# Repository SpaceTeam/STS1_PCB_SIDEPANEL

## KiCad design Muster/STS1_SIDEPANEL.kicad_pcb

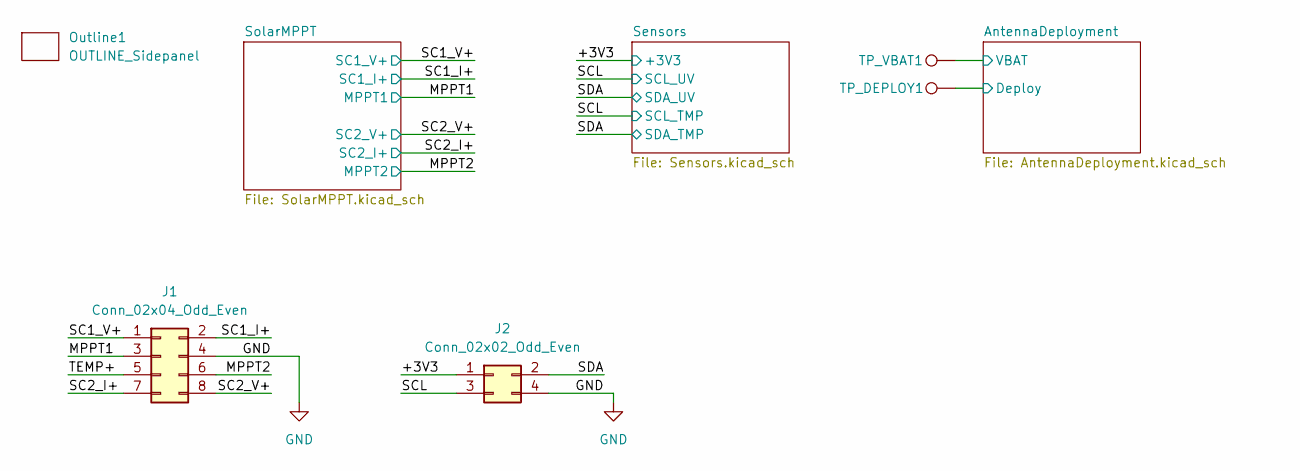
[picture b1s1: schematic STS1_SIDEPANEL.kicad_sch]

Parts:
J1: Conn_02x04_Odd_Even; M808280842
J2: Conn_02x02_Odd_Even; M80-8280442
Outline1: OUTLINE_Sidepanel; OUTLINE_SidepanelZ+
TP_DEPLOY1: TestPoint; TestPoint_Loop_D1.80mm_Drill1.0mm_Beaded
TP_VBAT1: TestPoint; TestPoint_Loop_D1.80mm_Drill1.0mm_Beaded

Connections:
/AntennaDeployment/Deploy: TP_DEPLOY1.1; also elsewhere on the board
/AntennaDeployment/VBAT: TP_VBAT1.1; also elsewhere on the board
/MPPT1: J1.3; also elsewhere on the board
/MPPT2: J1.6; also elsewhere on the board
/SC1_I+: J1.2; also elsewhere on the board
/SC1_V+: J1.1; also elsewhere on the board
/SC2_I+: J1.7; also elsewhere on the board
/SC2_V+: J1.8; also elsewhere on the board
/SCL: J2.3; also elsewhere on the board
/SDA: J2.2; also elsewhere on the board
/TEMP+: J1.5
GND: J1.4, J2.4; also elsewhere on the board

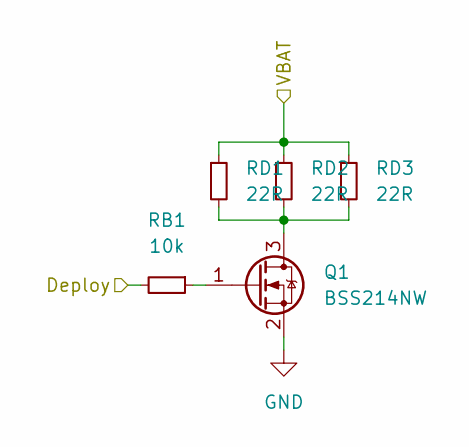
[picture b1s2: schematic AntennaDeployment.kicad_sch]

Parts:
Q1: BSS214NW; SOT-323_SC-70
RB1: 10k; R_0603_1608Metric
RD1, RD2, RD3: 22R; R_MiniMELF_MMA-0204

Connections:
/AntennaDeployment/Deploy: RB1.2; also elsewhere on the board
/AntennaDeployment/VBAT: RD1.1, RD2.1, RD3.1; also elsewhere on the board
GND: Q1.2 (S); also elsewhere on the board
unnamed: Q1.1 (G), RB1.1
unnamed: Q1.3 (D), RD1.2, RD2.2, RD3.2

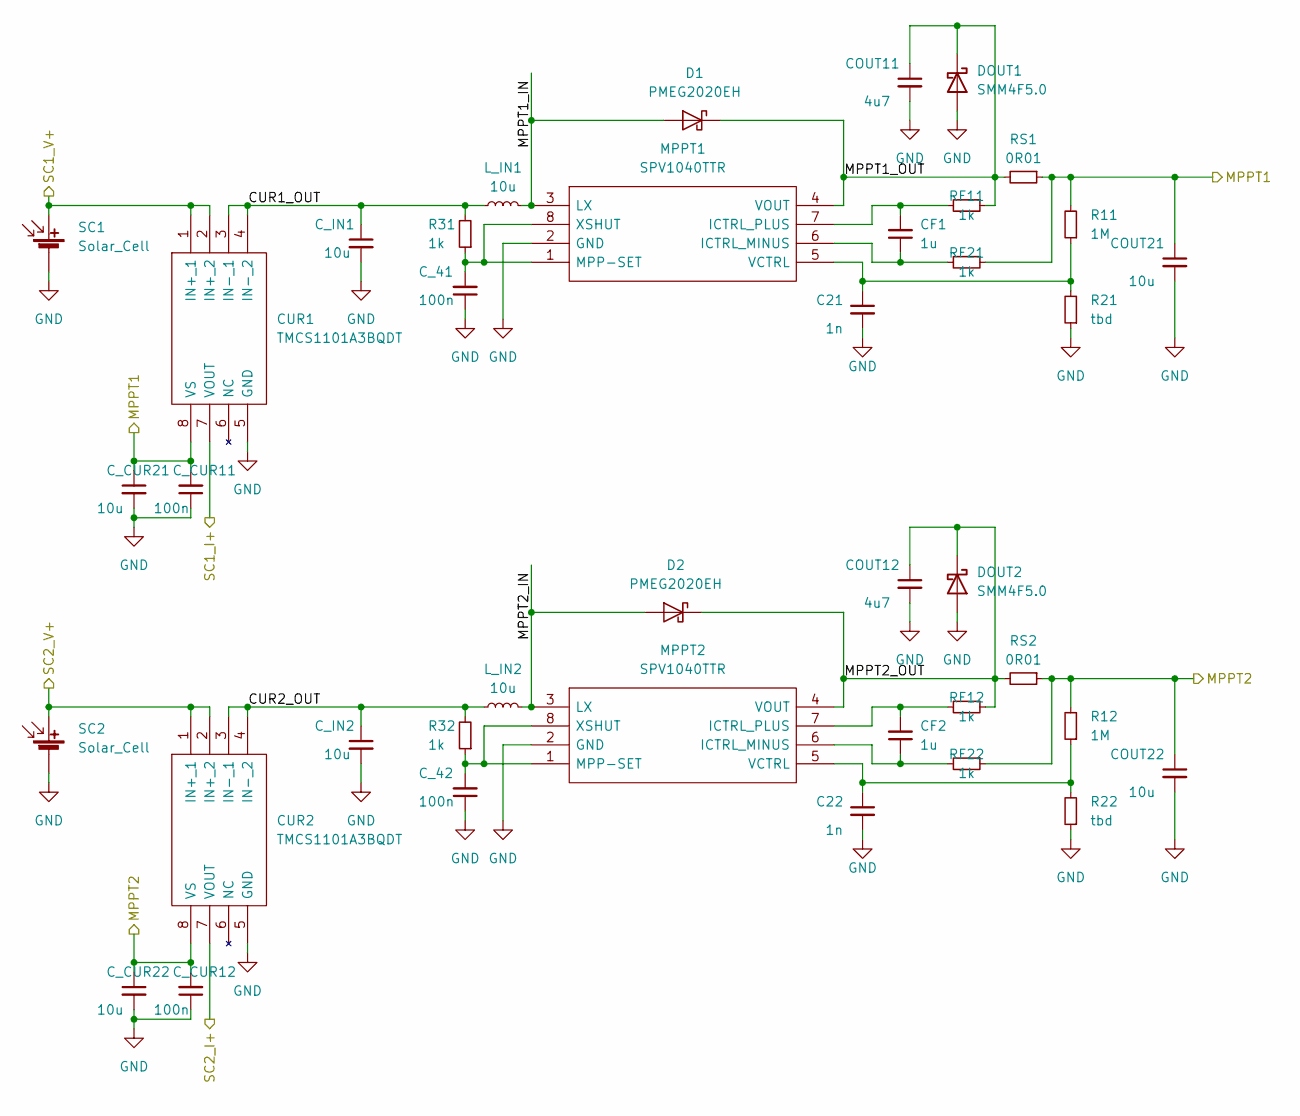
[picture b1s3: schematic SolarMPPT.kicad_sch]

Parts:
C21, C22: 1n; C_0603_1608Metric
CF1, CF2: 1u; C_0603_1608Metric
COUT11, COUT12: 4u7; C_0603_1608Metric
COUT21, COUT22: 10u; C_0603_1608Metric
CUR1, CUR2: TMCS1101A3BQDT; SOIC127P600X175-8N; Mouser Part Number 595-TMCS1101A3BQDT
C_41, C_42: 100n; C_0603_1608Metric
C_CUR11, C_CUR12: 100n; C_0603_1608Metric
C_CUR21, C_CUR22: 10u; C_0603_1608Metric
C_IN1, C_IN2: 10u; C_0603_1608Metric
D1, D2: PMEG2020EH; D_SOD-123F
DOUT1, DOUT2: SMM4F5.0; STMITE
L_IN1, L_IN2: 10u; INDPM5650X530N
MPPT1, MPPT2: SPV1040TTR; SOP65P640X120-8N; Mouser Part Number 511-SPV1040TTR
R11, R12: 1M; R_0603_1608Metric
R21, R22: tbd; R_0603_1608Metric
R31, R32: 1k; R_0603_1608Metric
RF11, RF12, RF21, RF22: 1k; R_0603_1608Metric
RS1, RS2: 0R01; R_0603_1608Metric
SC1, SC2: Solar_Cell; 3G30A_40x80

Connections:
/MPPT1: COUT21.1, CUR1.8 (VS), C_CUR11.2, C_CUR21.1, R11.2, RF21.1, RS1.1; also elsewhere on the board
/MPPT2: COUT22.1, CUR2.8 (VS), C_CUR12.2, C_CUR22.1, R12.2, RF22.1, RS2.1; also elsewhere on the board
/SC1_I+: CUR1.7 (VOUT); also elsewhere on the board
/SC1_V+: CUR1.1 (IN+_1), CUR1.2 (IN+_2), SC1.1 (+); also elsewhere on the board
/SC2_I+: CUR2.7 (VOUT); also elsewhere on the board
/SC2_V+: CUR2.1 (IN+_1), CUR2.2 (IN+_2), SC2.1 (+); also elsewhere on the board
/SolarMPPT/CUR1_OUT: CUR1.3 (IN-_1), CUR1.4 (IN-_2), C_IN1.1, L_IN1.1, R31.2
/SolarMPPT/CUR2_OUT: CUR2.3 (IN-_1), CUR2.4 (IN-_2), C_IN2.1, L_IN2.1, R32.2
/SolarMPPT/MPPT1_IN: D1.2 (A), L_IN1.2, MPPT1.3 (LX)
/SolarMPPT/MPPT1_OUT: COUT11.1, D1.1 (K), DOUT1.1 (K), MPPT1.4 (VOUT), RF11.1, RS1.2
/SolarMPPT/MPPT2_IN: D2.2 (A), L_IN2.2, MPPT2.3 (LX)
/SolarMPPT/MPPT2_OUT: COUT12.1, D2.1 (K), DOUT2.1 (K), MPPT2.4 (VOUT), RF12.1, RS2.2
GND: C21.2, C22.2, COUT11.2, COUT12.2, COUT21.2, COUT22.2, CUR1.5 (GND), CUR2.5 (GND), C_41.1, C_42.1, C_CUR11.1, C_CUR12.1, C_CUR21.2, C_CUR22.2, C_IN1.2, C_IN2.2, DOUT1.2 (A), DOUT2.2 (A), MPPT1.2 (GND), MPPT2.2 (GND), R21.1, R22.1, SC1.2 (-), SC2.2 (-); also elsewhere on the board
unnamed: C21.1, MPPT1.5 (VCTRL), R11.1, R21.2
unnamed: C22.1, MPPT2.5 (VCTRL), R12.1, R22.2
unnamed: CF1.1, MPPT1.6 (ICTRL_MINUS), RF21.2
unnamed: CF1.2, MPPT1.7 (ICTRL_PLUS), RF11.2
unnamed: CF2.1, MPPT2.6 (ICTRL_MINUS), RF22.2
unnamed: CF2.2, MPPT2.7 (ICTRL_PLUS), RF12.2
unnamed: C_41.2, MPPT1.1 (MPP-SET), MPPT1.8 (XSHUT), R31.1
unnamed: C_42.2, MPPT2.1 (MPP-SET), MPPT2.8 (XSHUT), R32.1

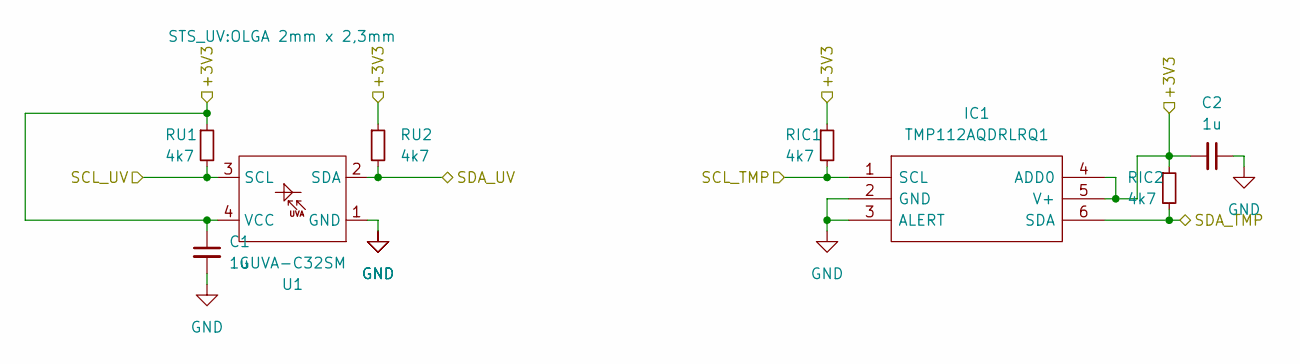
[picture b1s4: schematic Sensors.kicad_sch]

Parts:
C1, C2: 1u; C_0603_1608Metric
IC1: TMP112AQDRLRQ1; SOT-563; Mouser Part Number 595-TMP112AQDRLRQ1
RIC1, RIC2: 4k7; R_0603_1608Metric
RU1, RU2: 4k7; R_0603_1608Metric
U1: GUVA-C32SM; OLGA 2mm x 2,3mm

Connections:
/SCL: IC1.1 (SCL), RIC1.2, RU1.2, U1.3 (SCL); also elsewhere on the board
/SDA: IC1.6 (SDA), RIC2.2, RU2.2, U1.2 (SDA); also elsewhere on the board
GND: C1.2, C2.1, IC1.2 (GND), IC1.3 (ALERT), U1.1 (GND); also elsewhere on the board

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
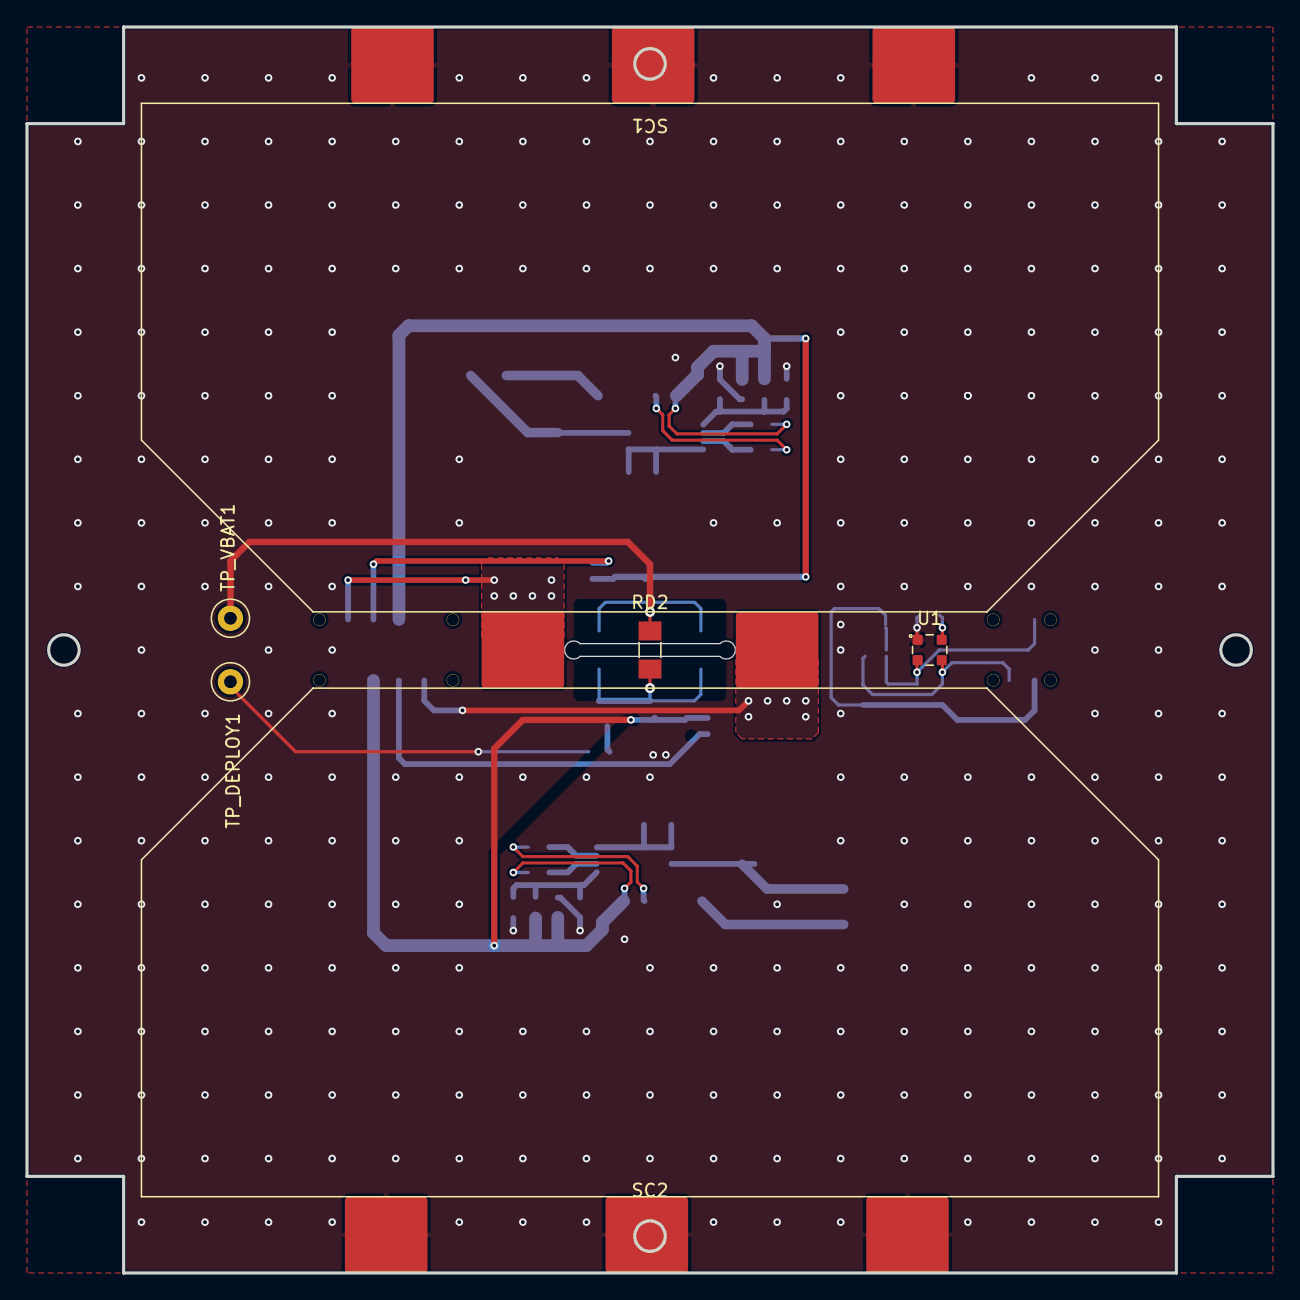
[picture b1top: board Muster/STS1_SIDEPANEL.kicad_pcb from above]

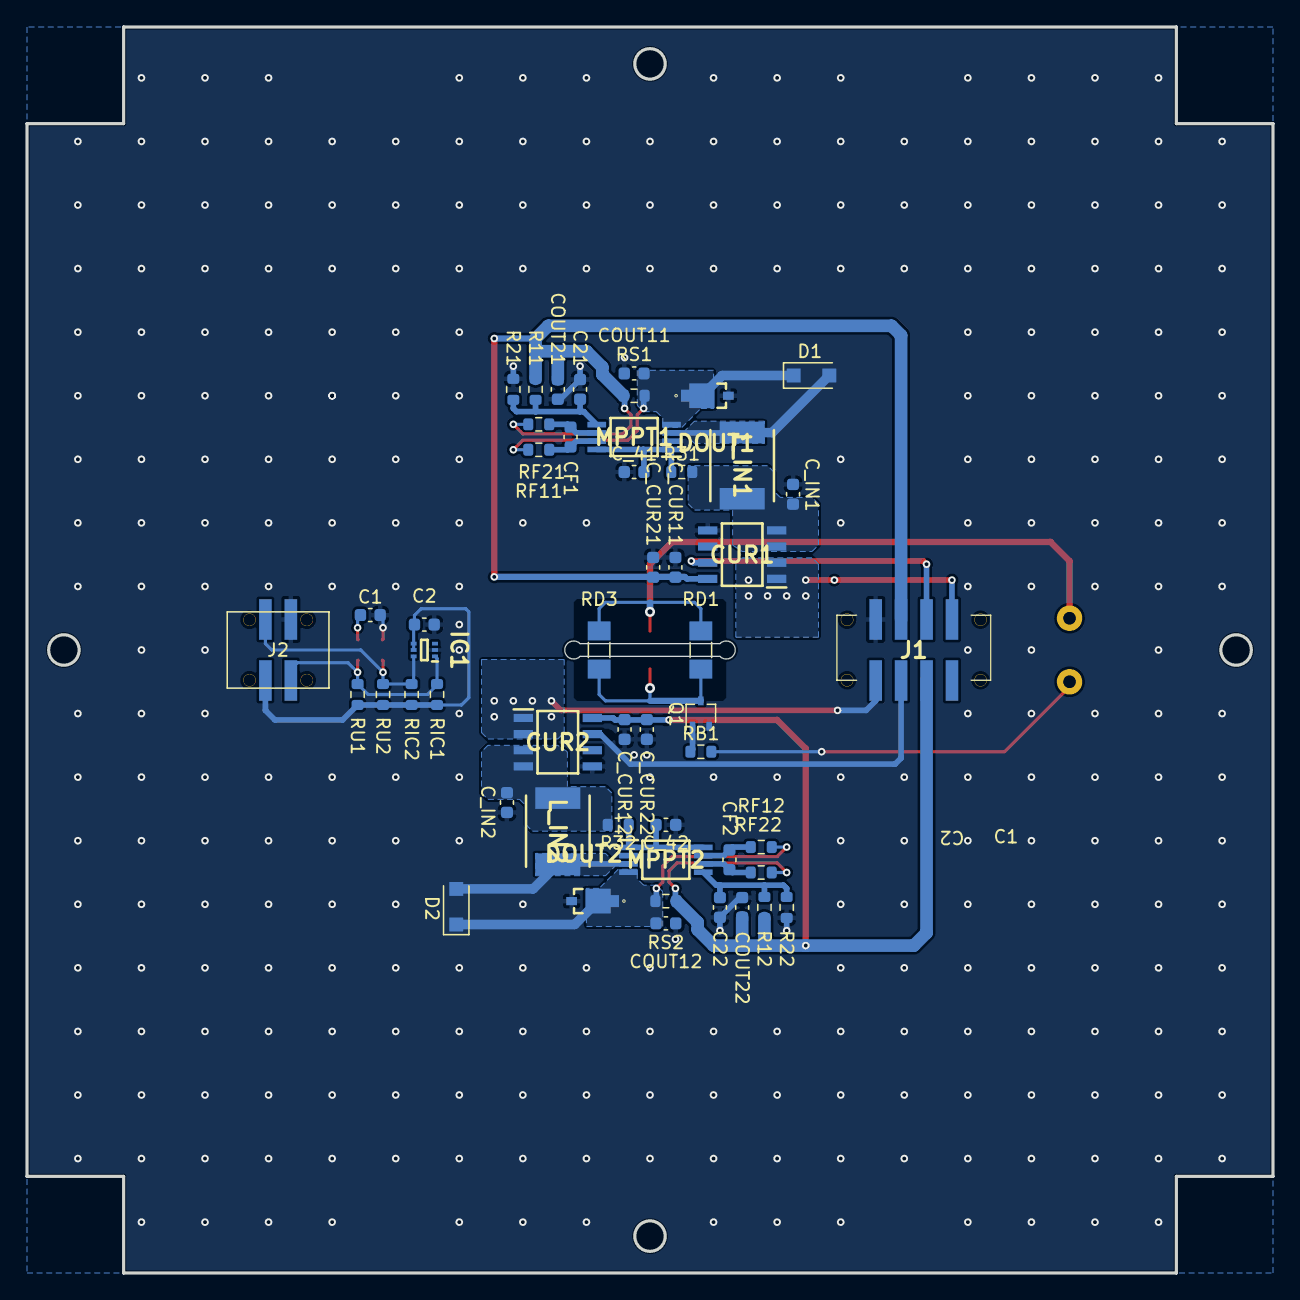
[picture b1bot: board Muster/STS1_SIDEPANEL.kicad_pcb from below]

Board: 2 copper layers, 98.0 x 98.0 mm, 58 parts (51 on the bottom side), 29 nets.

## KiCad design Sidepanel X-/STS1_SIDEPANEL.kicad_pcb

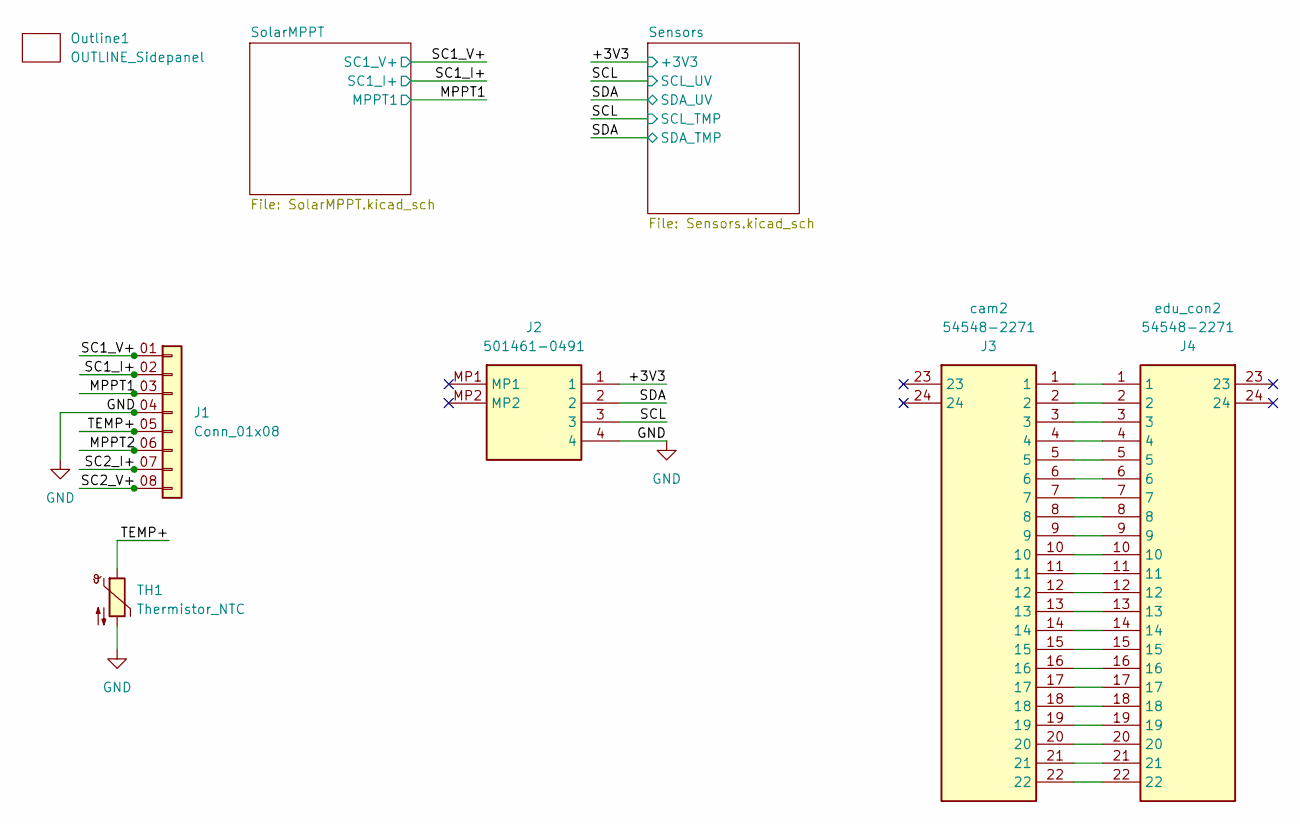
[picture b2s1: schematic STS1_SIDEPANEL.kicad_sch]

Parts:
J1: Conn_01x08; SAMTEC_ZF5S-08-01-T-WT
Outline1: OUTLINE_Sidepanel; OUTLINE_SidepanelX-
TH1: Thermistor_NTC; R_0805_2012Metric_Pad1.20x1.40mm_HandSolder
UV1: 501461-0491; 5014610491; Manufacturer_Part_Number 501461-0491; Mouser Part Number 538-501461-0491
cam2: 54548-2271; 545482271; Manufacturer_Part_Number 54548-2271; Mouser Part Number 538-54548-2271
edu_con2: 54548-2271; 545482271; Manufacturer_Part_Number 54548-2271; Mouser Part Number 538-54548-2271

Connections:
/+3V3: UV1.1; also elsewhere on the board
/MPPT1: J1.03 (Pin_3); also elsewhere on the board
/MPPT2: J1.06 (Pin_6)
/SC1_I+: J1.02 (Pin_2); also elsewhere on the board
/SC1_V+: J1.01 (Pin_1); also elsewhere on the board
/SC2_I+: J1.07 (Pin_7)
/SC2_V+: J1.08 (Pin_8)
/SCL: UV1.3; also elsewhere on the board
/SDA: UV1.2; also elsewhere on the board
/TEMP+: J1.05 (Pin_5), TH1.1
GND: J1.04 (Pin_4), TH1.2, UV1.4; also elsewhere on the board
unnamed: cam2.1, edu_con2.1
unnamed: cam2.2, edu_con2.2
unnamed: cam2.3, edu_con2.3
unnamed: cam2.4, edu_con2.4
unnamed: cam2.5, edu_con2.5
unnamed: cam2.6, edu_con2.6
unnamed: cam2.7, edu_con2.7
unnamed: cam2.8, edu_con2.8
unnamed: cam2.9, edu_con2.9
unnamed: cam2.10, edu_con2.10
unnamed: cam2.11, edu_con2.11
unnamed: cam2.12, edu_con2.12
unnamed: cam2.13, edu_con2.13
unnamed: cam2.14, edu_con2.14
unnamed: cam2.15, edu_con2.15
unnamed: cam2.16, edu_con2.16
unnamed: cam2.17, edu_con2.17
unnamed: cam2.18, edu_con2.18
unnamed: cam2.19, edu_con2.19
unnamed: cam2.20, edu_con2.20
unnamed: cam2.21, edu_con2.21
unnamed: cam2.22, edu_con2.22

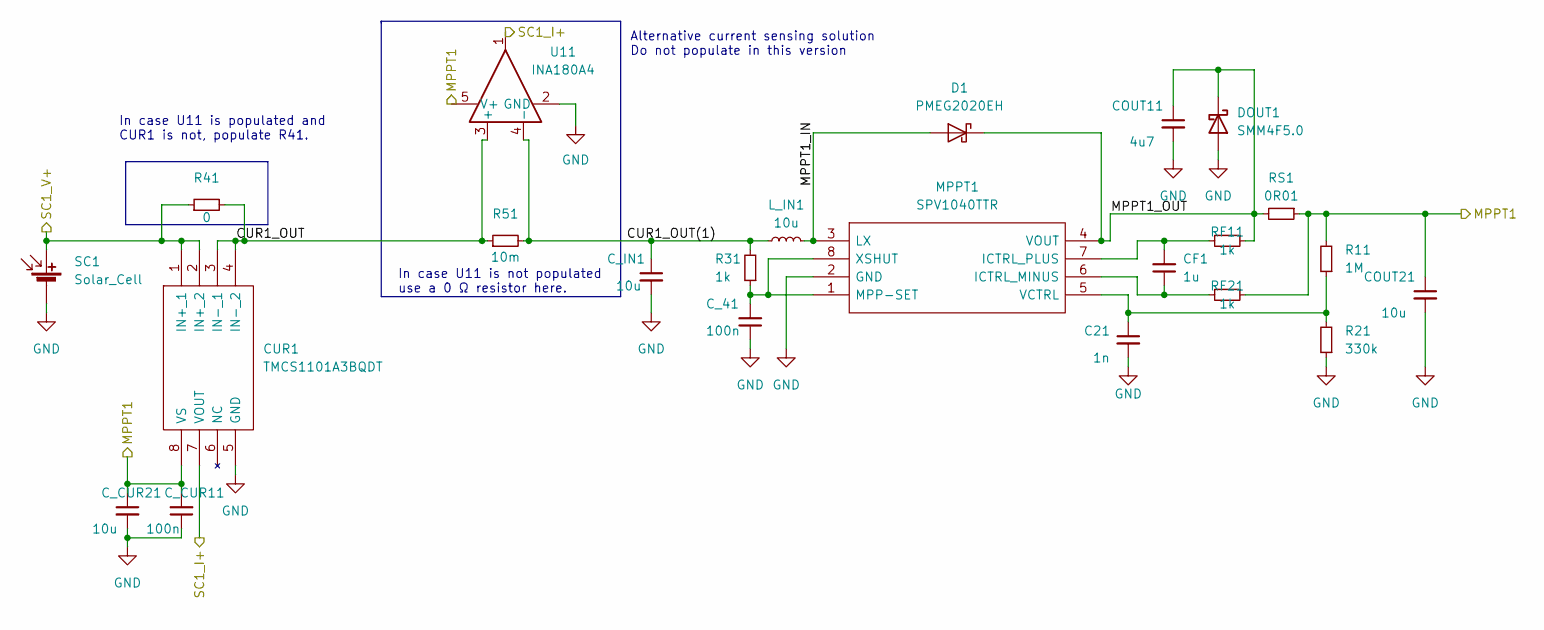
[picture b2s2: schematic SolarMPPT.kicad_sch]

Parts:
C21: 1n; C_0603_1608Metric
CF1: 1u; C_0603_1608Metric
COUT11: 4u7; C_0603_1608Metric
COUT21: 10u; C_0603_1608Metric
CUR1: TMCS1101A3BQDT; SOIC-8_3.9x4.9mm_P1.27mm; Mouser Part Number 595-TMCS1101A3BQDT
C_41: 100n; C_0603_1608Metric
C_CUR11: 100n; C_0603_1608Metric
C_CUR21: 10u; C_0603_1608Metric
C_IN1: 10u; C_0603_1608Metric
D1: PMEG2020EH; D_SOD-123F
DOUT1: SMM4F5.0; STMITE
L_IN1: 10u; XAL6060103MEC
MPPT1: SPV1040TTR; TSSOP-8_4.4x3mm_P0.65mm; Mouser Part Number 511-SPV1040TTR
R11: 1M; R_0603_1608Metric
R21: 330k; R_0603_1608Metric
R31: 1k; R_0603_1608Metric
R41: 0; R_0603_1608Metric
R51: 10m; R_0603_1608Metric
RF11, RF21: 1k; R_0603_1608Metric
RS1: 0R01; R_0603_1608Metric
SC1: Solar_Cell; 3G30A_40x80
U11: INA180A4; SOT-23-5

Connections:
/MPPT1: COUT21.1, CUR1.8 (VS), C_CUR11.2, C_CUR21.1, R11.2, RF21.1, RS1.1, U11.5 (V+); also elsewhere on the board
/SC1_I+: CUR1.7 (VOUT), U11.1; also elsewhere on the board
/SC1_V+: CUR1.1 (IN+_1), CUR1.2 (IN+_2), R41.1, SC1.1 (+), SC1.4; also elsewhere on the board
/SolarMPPT/CUR1_OUT: CUR1.3 (IN-_1), CUR1.4 (IN-_2), R41.2, R51.1, U11.3 (+)
/SolarMPPT/CUR1_OUT(1): C_IN1.1, L_IN1.1, R31.2, R51.2, U11.4 (-)
/SolarMPPT/MPPT1_IN: D1.2 (A), L_IN1.2, MPPT1.3 (LX)
/SolarMPPT/MPPT1_OUT: COUT11.1, D1.1 (K), DOUT1.1 (K), MPPT1.4 (VOUT), RF11.1, RS1.2
GND: C21.2, COUT11.2, COUT21.2, CUR1.5 (GND), C_41.1, C_CUR11.1, C_CUR21.2, C_IN1.2, DOUT1.2 (A), MPPT1.2 (GND), R21.1, SC1.2 (-), U11.2 (GND); also elsewhere on the board
unnamed: C21.1, MPPT1.5 (VCTRL), R11.1, R21.2
unnamed: CF1.1, MPPT1.6 (ICTRL_MINUS), RF21.2
unnamed: CF1.2, MPPT1.7 (ICTRL_PLUS), RF11.2
unnamed: C_41.2, MPPT1.1 (MPP-SET), MPPT1.8 (XSHUT), R31.1

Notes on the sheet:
In case U11 is populated and CUR1 is not, populate R41.
Alternative current sensing solution Do not populate in this version
In case U11 is not populated use a 0 Ω resistor here.

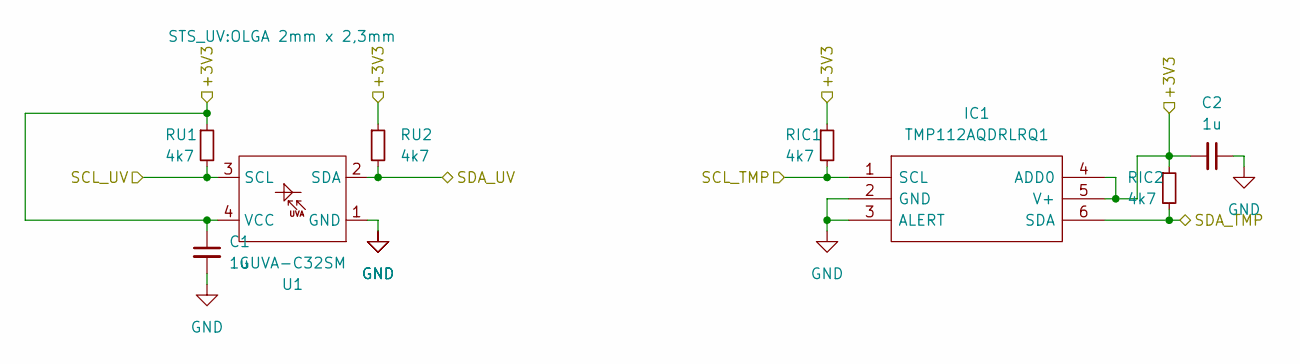
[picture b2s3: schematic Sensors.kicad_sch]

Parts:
C1, C2: 1u; C_0603_1608Metric
IC1: TMP112AQDRLRQ1; SOT-563; Mouser Part Number 595-TMP112AQDRLRQ1
RIC1, RIC2: 4k7; R_0603_1608Metric
RU1, RU2: 4k7; R_0603_1608Metric
U1: GUVA-C32SM; OLGA 2mm x 2,3mm

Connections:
/+3V3: C1.1, C2.2, IC1.4 (ADD0), IC1.5 (V+), RIC1.1, RIC2.1, RU1.1, RU2.1, U1.4 (VCC); also elsewhere on the board
/SCL: IC1.1 (SCL), RIC1.2, RU1.2, U1.3 (SCL); also elsewhere on the board
/SDA: IC1.6 (SDA), RIC2.2, RU2.2, U1.2 (SDA); also elsewhere on the board
GND: C1.2, C2.1, IC1.2 (GND), IC1.3 (ALERT), U1.1 (GND); also elsewhere on the board

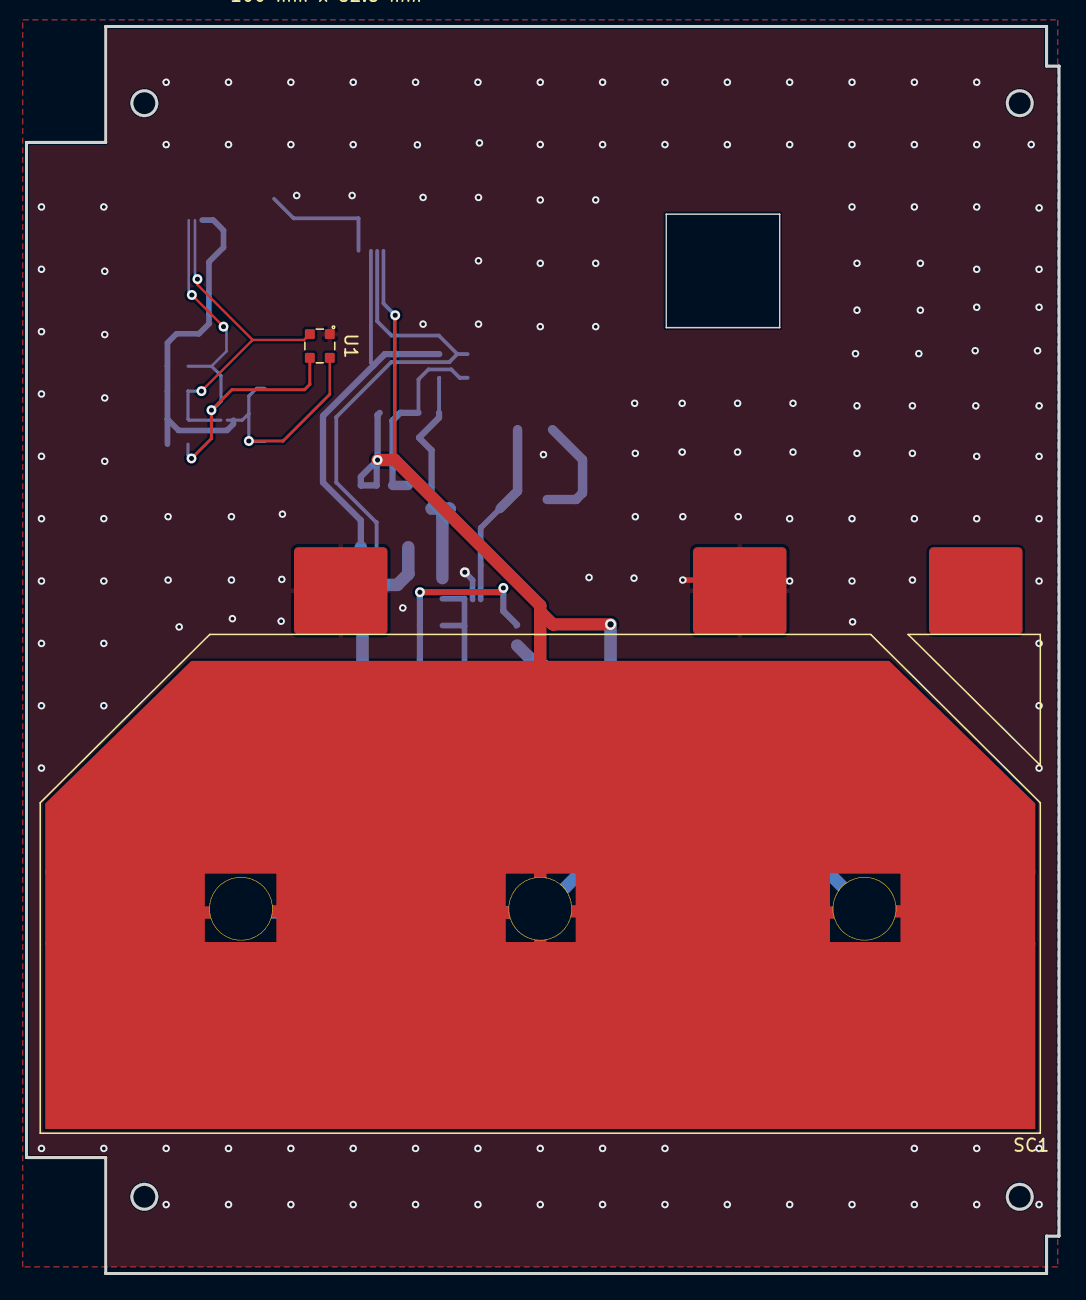
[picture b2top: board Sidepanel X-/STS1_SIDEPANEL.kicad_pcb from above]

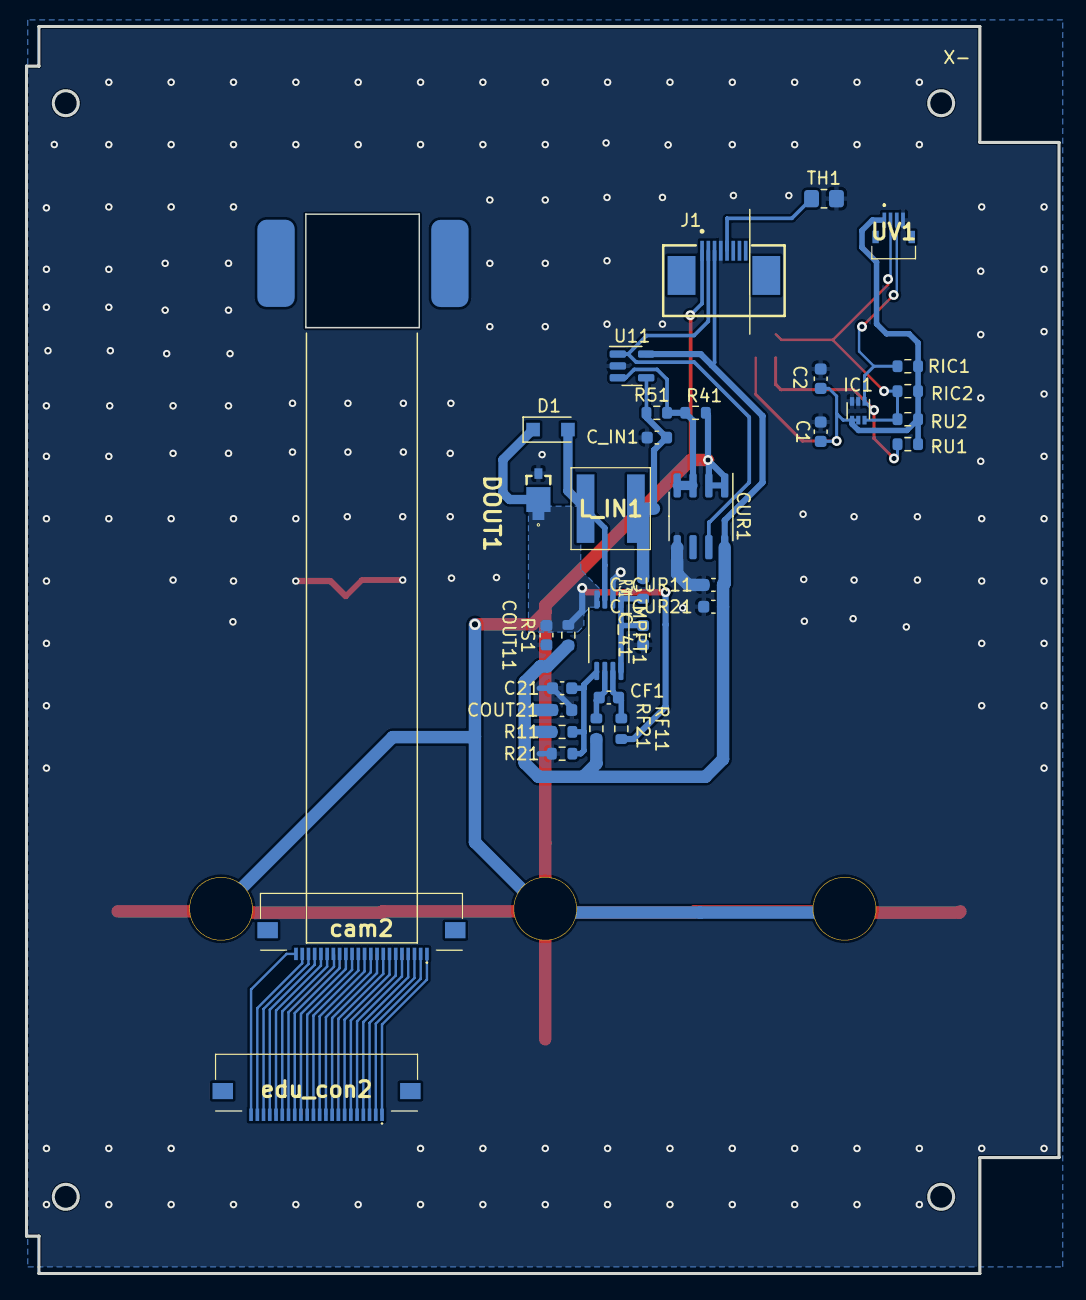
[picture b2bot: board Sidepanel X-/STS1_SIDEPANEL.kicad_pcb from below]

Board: 2 copper layers, 82.8 x 100.0 mm, 39 parts (34 on the bottom side), 38 nets.

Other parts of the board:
REF: cam_solder
REF#2: cam_solder
